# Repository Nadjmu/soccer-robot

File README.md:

# soccer-robot
This repository contains the schematic, the board design, the mechanical design (3D CAD Models) and the code for our autonomous soccer robot when we participated in the Soccer Lightweight League at the RoboCup Junior 2019. 

The rules can be found on the following website: https://junior.robocup.org/soccer/

The design of the motherboard and the ground board was done with Autodesk Eagle. The design of the mechanical components was done with the CAD Software Autodesk Inventor. The software was written with Arduino. 

This is a video where we played against Russia in the European Championship: https://www.youtube.com/watch?v=PZbQC_VygyU

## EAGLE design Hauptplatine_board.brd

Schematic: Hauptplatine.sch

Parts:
BODEN: PINHD-1X5; 1X05
C1: 0.33 uF; 1206
C2: 0.1 uF; 1206
C3: RAD 470/25; E5-10,5
C4, C6, C8, C10, C12, C14, C15, C18, C19, C22, C23, C27, C29, C31, C35, C37, C39, C43, C47, C49, C51, C53, C55, C79, C81: 1u; 1206
C5, C7, C9, C11, C13, C16, C17, C20, C21, C24, C26, C28, C30, C32, C36, C38, C40, C44, C48, C50, C52, C54, C56, C80, C82: 100n; 1206
C59: 0,33 uF; 1206
C60: 0,1uF; 1206
D1, D4: LED 6mm weiß; L3R2-08
D2, D3, D5: SFH205
D16: LED 6mm gruen; L3R2-08
F1, F2: SH22,5
IR1, IR2, IR3, IR4, IR5, IR6, IR7, IR8, IR9, IR10, IR11, IR12, IR13, IR14, IR15, IR16, IR17, IR18, IR19, IR20, IR21, IR23, IR24, IR25, IR26: TSOP4038; TSOP581X
JP1, JP2, JP3: PINHD-1X5; 1X05
JP4, JP7: PINHD-1X2; 1X02
JP5, JP6: PINHD-1X3; 1X03
LED1, LED2, LED3: LED3MM
MAGNETFELD: PINHD-1X4; 1X04
PIXY1: PINHD-2X3; 2X03
PL3: STLZ950G2; S940_2
R1, R20, R22, R24, R26, R28, R30, R32, R35, R41, R47, R50, R53, R56, R59, R62, R65, R68, R71, R74, R77, R79, R80, R85, R86, R87, R93, R95, R141, R144: 4.7k; 1206
R2, R3, R4: 60R; 1206
R5, R6, R7: 5k; 1206
R19, R21, R23, R25, R27, R29, R31, R34, R40, R46, R49, R52, R55, R58, R61, R64, R67, R70, R73, R76, R84, R92, R94, R140, R143: 100k; 1206
R33, R36, R37, R38, R39, R42, R43, R44, R45, R48, R51, R54, R57, R60, R63, R66, R69, R72, R75, R78, R124, R127, R128, R142, R145: 10R; 1206
S1, S2: KSM611A
SW1, SW2: Schukat_MS111; MSS13ASP
U$1, U$6: MOTOR_DRIVER_MODULE
U$28: BLUETOTHA
U$32: TEENSY_3.6_ALL_PINS
U$58: LOGICLEVEL
X1: ANALOG/DIGITAL-MUX-BREAKOUT

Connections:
3.3V: U$32.3.3V, U$32.3.3V3 (3.3V), U$32.3.3V4 (3.3V)
+3V3: BODEN.1, F2.2, MAGNETFELD.1, R5.1, R6.1, R7.1, R20.2, R22.2, R24.2, R26.2, R28.2, R30.2, R32.2, R33.2, R35.2, R36.2, R37.2, R38.2, R39.2, R41.2, R42.2, R43.2, R44.2, R45.2, R47.2, R48.2, R50.2, R51.2, R53.2, R54.2, R56.2, R57.2, R59.2, R60.2, R62.2, R63.2, R65.2, R66.2, R68.2, R69.2, R71.2, R72.2, R74.2, R75.2, R77.2, R78.2, R79.2, R80.2, R87.2, R93.2, R95.2, R124.2, R127.2, R128.2, R141.2, R142.2, R144.2, R145.2, U$28.VCC, U$58.9 (LV), X1.VCC
+5V: BODEN.3, C2.2, JP1.1, JP2.1, JP3.1, JP6.3, PIXY1.2, R2.1, R3.1, R4.1, U$1.+5V, U$6.+5V, U$32.VIN, U$32.VUSB, U$58.3 (HV)
+12V: C1.2, C3.+, C59.2, F1.1, JP5.1, JP6.1, R86.2, SW2.U (U1)
+12V1: R1.2, SW2.2 (R1), U$1.VCC@1 (VCC), U$1.VCC@2 (VCC), U$1.VCC@3 (VCC), U$6.VCC@1 (VCC), U$6.VCC@2 (VCC), U$6.VCC@3 (VCC)
AA_00: U$32.32/A13 (32/A13/TX4/SCK1), X1.SIG (COM)
AREF: U$32.AREF
A_01: C4.1, R19.2, X1.P$16 (16)
A_02: C6.1, R21.2, X1.P$15 (15)
A_03: C8.1, R23.2, X1.P$14 (14)
A_04: C10.1, R25.2, X1.P$13 (13)
A_05: C14.1, R49.2, X1.P$12 (12)
A_06: C12.1, R27.2, X1.P$11 (11)
A_07: C18.1, R55.2, X1.P$10 (10)
A_08: C15.1, R29.2, X1.P$9 (9)
A_09: C19.1, R31.2, X1.P$7 (7)
A_10: C23.1, R34.2, X1.P$8 (8)
A_11: C27.1, R40.2, U$32.23/A9 (23/A9/T/PWM)
A_12: C31.1, R46.2, U$32.39/A20
A_13: C35.1, R52.2, U$32.A21 (A21/DAC0)
A_14: C39.1, R58.2, U$32.21/A7 (21/A7/PWM)
A_15: C22.1, R61.2, U$32.22/A8 (22/A8/T/PWM)
A_16: C43.1, R64.2, U$32.34/A15 (34/A15/RX5/CAN1-RX)
A_17: C29.1, R67.2, U$32.35/A16 (35/A16/PWM)
A_18: C47.1, R70.2, U$32.36/A17 (36/A17/PWM)
A_19: C49.1, R73.2, U$32.37/A18 (37/A18/SCL1/PWM)
A_20: C51.1, R76.2, U$32.38/A19 (38/A19/SDA1/PWM)
A_21: C37.1, R84.2, U$32.33/A14 (33/A14/TX5/CAN1-TX)
A_24: C53.1, R92.2, X1.P$4 (4)
A_25: C79.1, R140.2, U$32.A11
A_26: C55.1, R94.2, X1.P$5 (5)
A_27: C81.1, R143.2, X1.P$6 (6)
D1.1__FW: U$1.M1_FW_SIG (IN1_FW), U$32.14/A0 (14/A0/PWM)
D1.2__RW: U$1.M1_RW_SIG (IN1_RW), U$32.20/A6 (20/A6/PWM)
D2.1__FW: U$1.M2_FW_SIG (IN2_FW), U$32.A22 (A22/DAC1)
D2.2__RW: U$1.M2_RW_SIG (IN2_RW), U$32.15/A1 (15/A1/T)
D3.1__FW: U$6.M1_FW_SIG (IN1_FW), U$32.16/A2 (16/A2/T/PWM)
D3.2__RW: U$6.M1_RW_SIG (IN1_RW), U$32.17/A3 (17/A3/T/PWM)
GND: BODEN.2, C1.1, C2.1, C3.-, C4.2, C5.2, C6.2, C7.2, C8.2, C9.2, C10.2, C11.2, C12.2, C13.2, C14.2, C15.2, C16.2, C17.2, C18.2, C19.2, C20.2, C21.2, C22.2, C23.2, C24.2, C26.2, C27.2, C28.2, C29.2, C30.2, C31.2, C32.2, C35.2, C36.2, C37.2, C38.2, C39.2, C40.2, C43.2, C44.2, C47.2, C48.2, C49.2, C50.2, C51.2, C52.2, C53.2, C54.2, C55.2, C56.2, C59.1, C60.1, C79.2, C80.2, C81.2, C82.2, D1.2 (K), D2.A, D3.A, D4.2 (K), D5.A, D16.2 (K), IR1.2 (GND), IR2.2 (GND), IR3.2 (GND), IR4.2 (GND), IR5.2 (GND), IR6.2 (GND), IR7.2 (GND), IR8.2 (GND), IR9.2 (GND), IR10.2 (GND), IR11.2 (GND), IR12.2 (GND), IR13.2 (GND), IR14.2 (GND), IR15.2 (GND), IR16.2 (GND), IR17.2 (GND), IR18.2 (GND), IR19.2 (GND), IR20.2 (GND), IR21.2 (GND), IR23.2 (GND), IR24.2 (GND), IR25.2 (GND), IR26.2 (GND), JP1.5, JP2.5, JP3.5, JP5.2, JP6.2, LED1.K (C), LED2.K (C), LED3.K (C), MAGNETFELD.4, PIXY1.6, PL3.2, S1.A, S1.C, S2.A, S2.C, U$1.GND@1 (GND), U$1.GND@2 (GND), U$1.GND@3 (GND), U$1.GND@4 (GND), U$6.GND@1 (GND), U$6.GND@2 (GND), U$6.GND@3 (GND), U$6.GND@4 (GND), U$28.GND, U$32.AGND, U$32.GND, U$32.GND1 (GND), U$32.GND3 (GND), U$32.GND4 (GND), U$32.GND6 (GND), U$58.4 (GND), U$58.10 (GND1), X1.GND
K1: R79.1, S1.B, S1.D, U$32.24
K2: R80.1, S2.B, S2.D, U$32.4 (4/CAN0-RX/SDA2/PWM)
LI1: D5.K (C), R6.2, X1.P$1 (1)
LI2: D3.K (C), R5.2, X1.P$2 (2)
LI3: D2.K (C), R7.2, X1.P$3 (3)
MISO: PIXY1.1, U$32.12 (12/MISO0)
MOSI: PIXY1.4, U$32.11 (11/MOSI0)
unnamed: JP4.2, U$6.M1_FW (OUT1_FW)
unnamed: F1.2, SW1.1 (A1)
unnamed: JP4.1, U$6.M1_RW (OUT1_RW)
unnamed: C60.2, F2.1, JP5.3
unnamed: JP7.2, U$6.M2_FW (OUT2_FW)
unnamed: JP7.1, U$6.M2_RW (OUT2_RW)
unnamed: LED3.A, R2.2
unnamed: LED1.A, R3.2
unnamed: LED2.A, R4.2
unnamed: D4.1 (A), R1.1
unnamed: PL3.1, R85.2, SW1.U (U1)
unnamed: IR1.1 (VO), R19.1, R20.1
unnamed: C5.1, IR1.3 (VS), R33.1
unnamed: IR2.1 (VO), R21.1, R22.1
unnamed: C7.1, IR2.3 (VS), R36.1
unnamed: IR3.1 (VO), R23.1, R24.1
unnamed: C9.1, IR3.3 (VS), R37.1
unnamed: IR4.1 (VO), R25.1, R26.1
unnamed: C11.1, IR4.3 (VS), R38.1
unnamed: IR6.1 (VO), R27.1, R28.1
unnamed: C13.1, IR6.3 (VS), R39.1
unnamed: IR8.1 (VO), R29.1, R30.1
unnamed: IR9.1 (VO), R31.1, R32.1
unnamed: C20.1, IR9.3 (VS), R43.1
unnamed: IR10.1 (VO), R34.1, R35.1
unnamed: C24.1, IR10.3 (VS), R44.1
unnamed: C16.1, IR8.3 (VS), R42.1
unnamed: IR5.1 (VO), R49.1, R50.1
unnamed: IR11.1 (VO), R40.1, R41.1
unnamed: C28.1, IR11.3 (VS), R45.1
unnamed: IR12.1 (VO), R46.1, R47.1
unnamed: C32.1, IR12.3 (VS), R48.1
unnamed: C17.1, IR5.3 (VS), R51.1
unnamed: IR7.1 (VO), R55.1, R56.1
unnamed: C21.1, IR7.3 (VS), R57.1
unnamed: IR15.1 (VO), R61.1, R62.1
unnamed: C26.1, IR15.3 (VS), R63.1
unnamed: IR17.1 (VO), R67.1, R68.1
unnamed: C30.1, IR17.3 (VS), R69.1
unnamed: IR21.1 (VO), R84.1, R87.1
unnamed: C38.1, IR21.3 (VS), R124.1
unnamed: IR13.1 (VO), R52.1, R53.1
unnamed: C36.1, IR13.3 (VS), R54.1
unnamed: IR14.1 (VO), R58.1, R59.1
unnamed: C40.1, IR14.3 (VS), R60.1
unnamed: IR23.1 (VO), R92.1, R93.1
unnamed: C54.1, IR23.3 (VS), R127.1
unnamed: IR25.1 (VO), R94.1, R95.1
unnamed: C56.1, IR25.3 (VS), R128.1
unnamed: IR16.1 (VO), R64.1, R65.1
unnamed: C44.1, IR16.3 (VS), R66.1
unnamed: IR18.1 (VO), R70.1, R71.1
unnamed: C48.1, IR18.3 (VS), R72.1
unnamed: IR19.1 (VO), R73.1, R74.1
unnamed: C50.1, IR19.3 (VS), R75.1
unnamed: IR20.1 (VO), R76.1, R77.1
unnamed: C52.1, IR20.3 (VS), R78.1
unnamed: IR24.1 (VO), R140.1, R141.1
unnamed: C80.1, IR24.3 (VS), R142.1
unnamed: IR26.1 (VO), R143.1, R144.1
unnamed: C82.1, IR26.3 (VS), R145.1
unnamed: D16.1 (A), R85.1
unnamed: D1.1 (A), R86.1
PWM_M1: U$1.M1_PWM_SIG (IN1_PWM), U$32.5 (5/PWM)
PWM_M2: U$1.M2_PWM_SIG (IN2_PWM), U$32.6 (6/PWM)
PWM_M3: U$6.M1_PWM_SIG (IN1_PWM), U$32.29 (29/T/PWM)
RX2: BODEN.5, U$32.9 (9/RX2/PWM)
RXB: U$28.TX, U$32.7 (7/RX3/PWM)
SCK: PIXY1.3, U$32.13 (13/SCK0/LED)
SCL_2: MAGNETFELD.2, U$32.19/A5 (19/A5/T/SCL0), U$58.8 (LV2)
SCL_ULT: JP1.3, JP2.3, JP3.3, U$58.2 (HV2)
SDA_2: MAGNETFELD.3, U$32.18/A4 (18/A4/T/SDA0), U$58.7 (LV1)
SDA_ULT: JP1.2, JP2.2, JP3.2, U$58.1 (HV1)
S_0: U$32.0 (0/RX1/MOSI1/T), X1.S0
S_1: U$32.1 (1/TX1/MISO1/T), X1.S1
S_2: U$32.2 (2/PWM), X1.S2
S_3: U$32.3 (3/CAN0-TX/SCL2/PWM), X1.S3
TX2: BODEN.4, U$32.10 (10/TX2/PWM)
TXB: U$28.RX, U$32.8 (8/TX3/PWM)
VBAT: U$32.VBAT
VUSB1: U$32.VUSB1

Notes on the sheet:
Akku
VCC
GND
LED akku angeschlossen
LED Roboter an
+5V
Torwrt
feldspieler
magnetfeld
sicherung 16 A (Träge)
sicherung 1 A
echter NAME TSSP4038
0.1uF und 100nF ist Dasselbe!!!!!!!!!!!!!!!!!!!!!!!!!!!!!!!!!!!!!!!!!!!!!!!!!!!!!!!!!!!!!!!!!!!!!!!!
3,3 V wandler
LED Motoren an

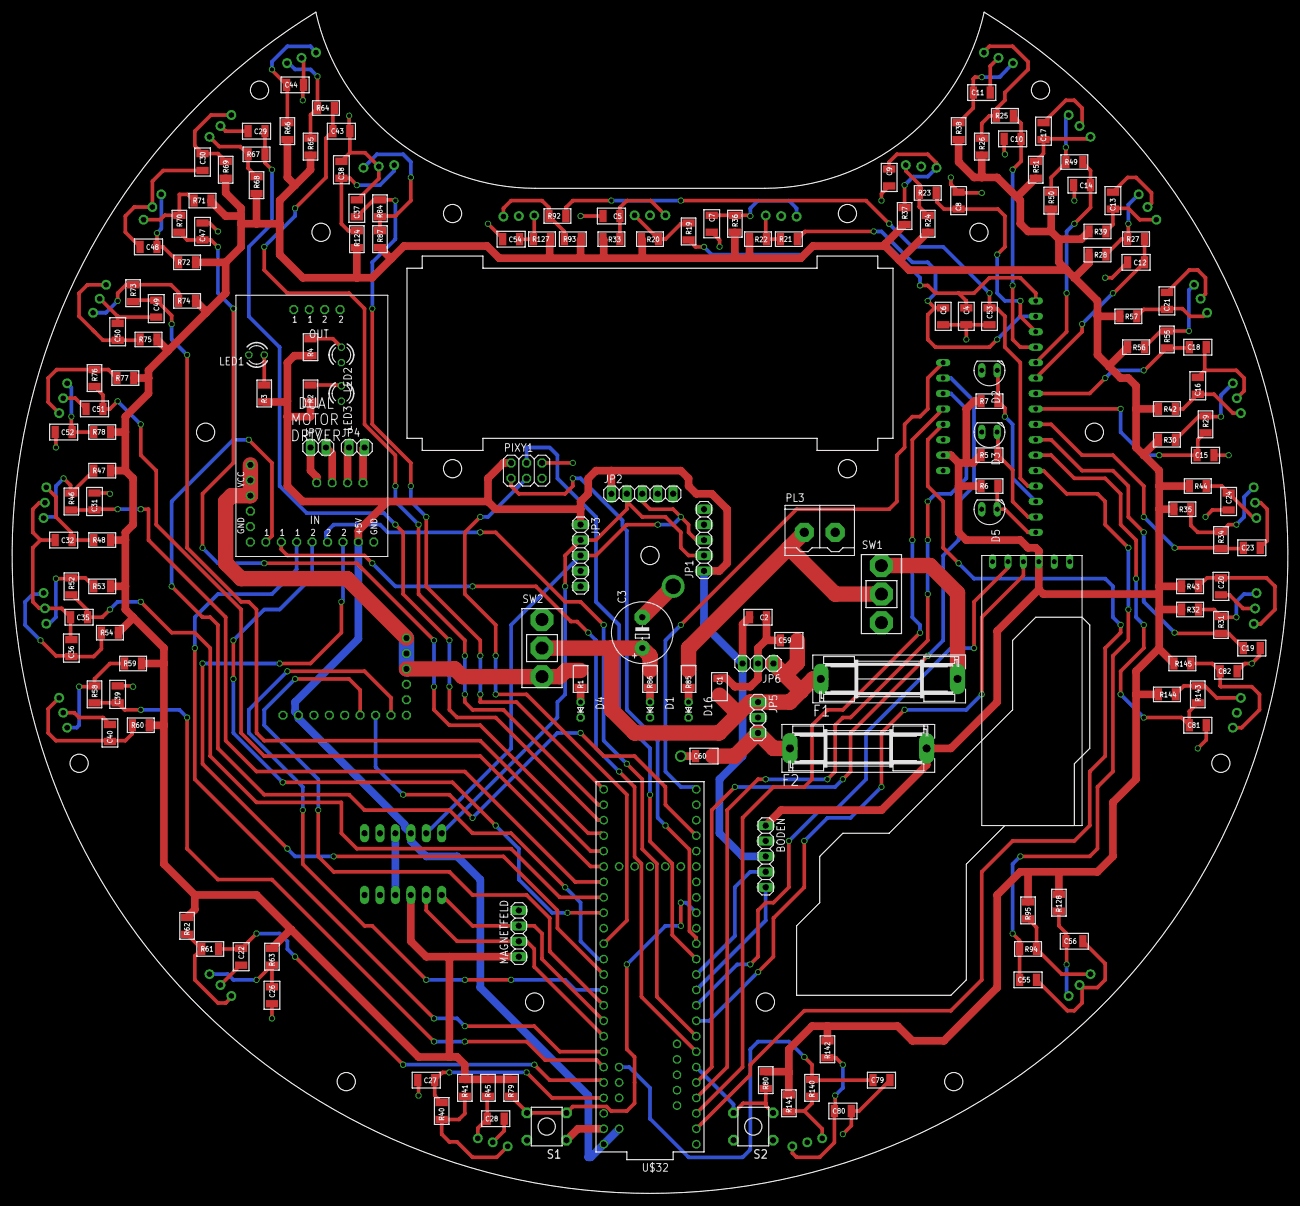
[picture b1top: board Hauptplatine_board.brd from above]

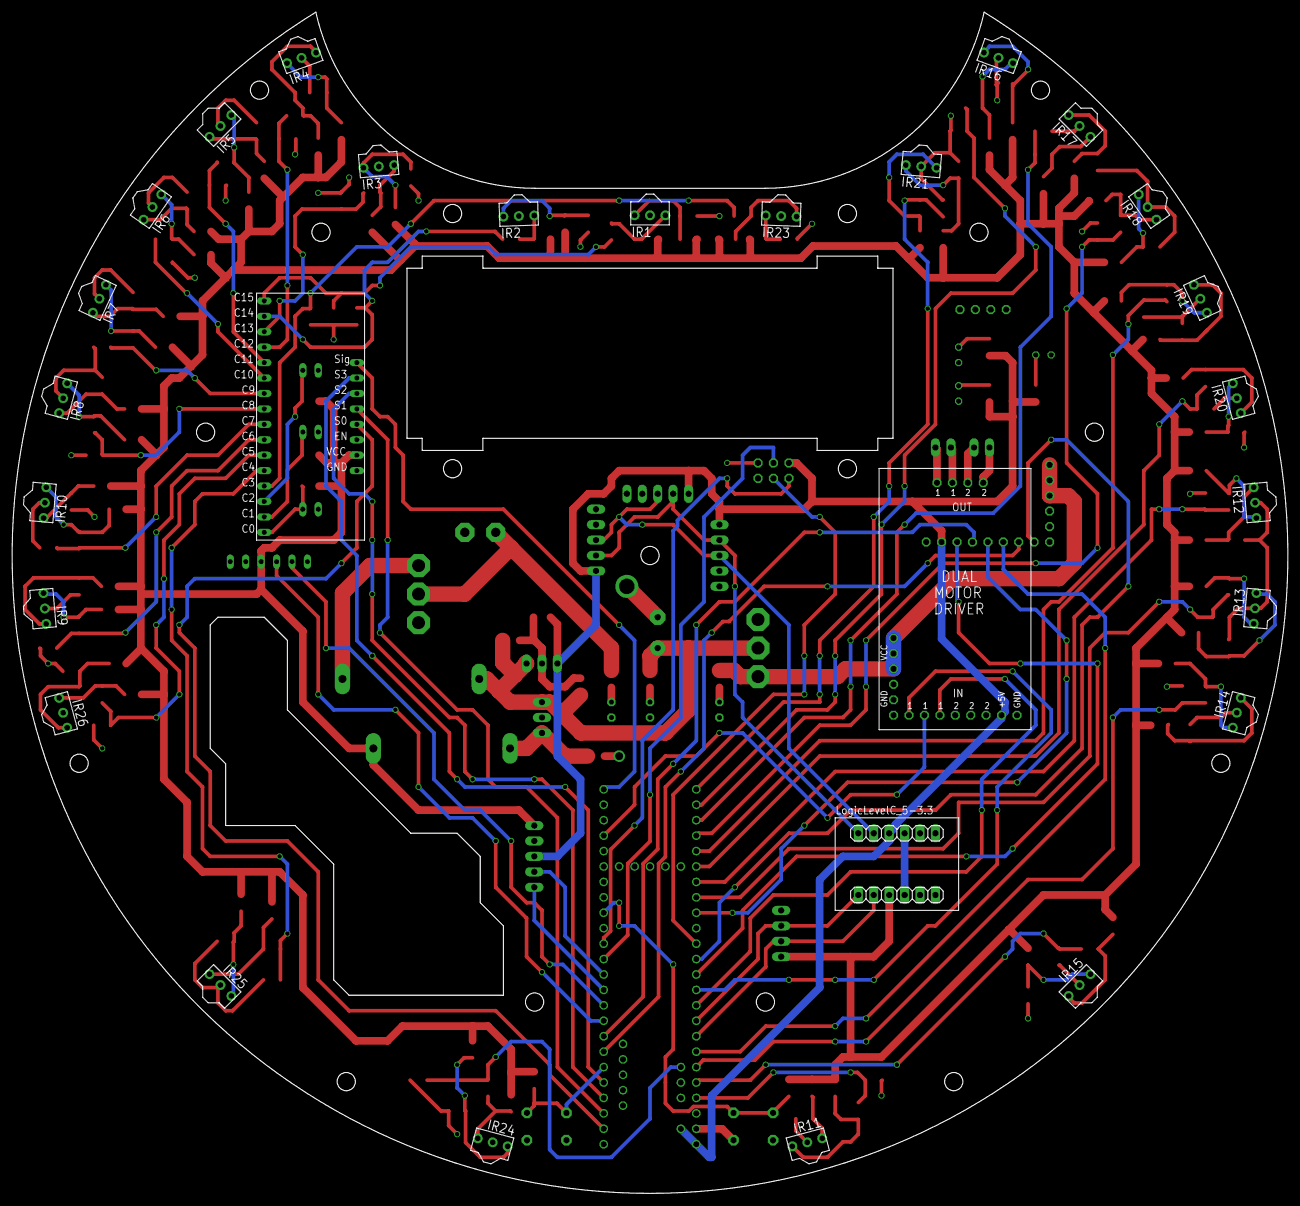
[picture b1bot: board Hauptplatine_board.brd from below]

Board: 2 copper layers, 210.0 x 194.4 mm, 198 parts (28 on the bottom side), 124 nets.

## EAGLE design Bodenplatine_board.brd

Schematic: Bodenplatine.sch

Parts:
D1, D2, D3, D4, D5, D6, D7, D8, D9, D10, D11, D13, D14, D15, D16, D17, D18, D19, D20, D21, D22, D23, D24, D25, D26, D27, D28, D29, D30, D34, D35, D36, D37: SFH205
JP1: PINHD-1X5; 1X05
LED1, LED2, LED3, LED4, LED5, LED6, LED7, LED8, LED9, LED10, LED11, LED12, LED14, LED15, LED16, LED17, LED18, LED19, LED20, LED21, LED22, LED23, LED24, LED25, LED26, LED27, LED28, LED29, LED30, LED31, LED32, LED33, LED34, LED38, LED40, LED41, LED42: LED3MM
R1, R2, R4, R5, R8, R10, R14, R15, R17, R19, R21, R23, R26, R28, R29, R30, R32, R34, R38, R40, R41, R42, R43, R45, R47, R48, R49, R50, R52, R54, R55, R56, R58, R59, R61, R62, R68: 60R; 1206
R3, R6, R7, R9, R11, R12, R13, R16, R18, R20, R22, R24, R25, R27, R31, R33, R35, R36, R39, R44, R46, R51, R53, R64, R65, R66, R67, R71, R72, R73, R78, R79, R80: 5k; 1206
U$32: TEENSY_3.6_ALL_PINS
X1: ANALOG/DIGITAL-MUX-BREAKOUT

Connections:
3.3V: U$32.3.3V, U$32.3.3V3 (3.3V), U$32.3.3V4 (3.3V)
+3V3: JP1.1, R3.1, R6.1, R7.1, R9.1, R11.1, R12.1, R13.1, R16.1, R18.1, R20.1, R22.1, R24.1, R25.1, R27.1, R31.1, R33.1, R35.1, R36.1, R39.1, R44.1, R46.1, R51.1, R53.1, R64.1, R65.1, R66.1, R67.1, R71.1, R72.1, R73.1, R78.1, R79.1, R80.1, X1.VCC
+5V: JP1.3, R1.1, R2.1, R4.1, R5.1, R8.1, R10.1, R14.1, R15.1, R17.1, R19.1, R21.1, R23.1, R26.1, R28.1, R29.1, R30.1, R32.2, R34.1, R38.1, R40.2, R41.1, R42.2, R43.2, R45.1, R47.1, R48.1, R49.1, R50.1, R52.1, R54.1, R55.1, R56.1, R58.1, U$32.VIN, U$32.VUSB
A1: D16.K (C), R7.2, U$32.15/A1 (15/A1/T)
A2: D15.K (C), R9.2, U$32.16/A2 (16/A2/T/PWM)
A3: D14.K (C), R11.2, U$32.17/A3 (17/A3/T/PWM)
A4: D13.K (C), R13.2, U$32.18/A4 (18/A4/T/SDA0)
A5: D9.K (C), R18.2, U$32.19/A5 (19/A5/T/SCL0)
A6: D8.K (C), R20.2, U$32.20/A6 (20/A6/PWM)
A7: D7.K (C), R22.2, U$32.21/A7 (21/A7/PWM)
A8: D6.K (C), R25.2, U$32.22/A8 (22/A8/T/PWM)
A9: D5.K (C), R27.2, U$32.23/A9 (23/A9/T/PWM)
A10: D2.K (C), R33.2, U$32.A21 (A21/DAC0)
A11: D1.K (C), R35.2, U$32.A22 (A22/DAC1)
A13: D37.K (C), R64.2, U$32.32/A13 (32/A13/TX4/SCK1)
A14: D36.K (C), R65.2, U$32.33/A14 (33/A14/TX5/CAN1-TX)
A15: D35.K (C), R66.2, U$32.34/A15 (34/A15/RX5/CAN1-RX)
A16: D34.K (C), R67.2, U$32.35/A16 (35/A16/PWM)
A17: D30.K (C), R71.2, U$32.36/A17 (36/A17/PWM)
A18: D29.K (C), R72.2, U$32.37/A18 (37/A18/SCL1/PWM)
A19: D28.K (C), R73.2, X1.P$1 (1)
A20: D23.K (C), R78.2, X1.P$2 (2)
A21: D22.K (C), R79.2, X1.P$3 (3)
A22: D21.K (C), R80.2, X1.P$4 (4)
A23: D3.K (C), R3.2, X1.P$5 (5)
A24: D4.K (C), R6.2, X1.P$6 (6)
A25: D10.K (C), R12.2, X1.P$7 (7)
A26: D11.K (C), R16.2, X1.P$8 (8)
A27: D17.K (C), R24.2, X1.P$9 (9)
A28: D18.K (C), R31.2, X1.P$10 (10)
A29: D19.K (C), R36.2, X1.P$11 (11)
A30: D20.K (C), R39.2, X1.P$12 (12)
A31: D24.K (C), R44.2, X1.P$13 (13)
A32: D25.K (C), R46.2, X1.P$14 (14)
A33: D26.K (C), R51.2, X1.P$15 (15)
A34: D27.K (C), R53.2, X1.P$16 (16)
AREF: U$32.AREF
GND: D1.A, D2.A, D3.A, D4.A, D5.A, D6.A, D7.A, D8.A, D9.A, D10.A, D11.A, D13.A, D14.A, D15.A, D16.A, D17.A, D18.A, D19.A, D20.A, D21.A, D22.A, D23.A, D24.A, D25.A, D26.A, D27.A, D28.A, D29.A, D30.A, D34.A, D35.A, D36.A, D37.A, JP1.2, LED1.K (C), LED2.K (C), LED3.K (C), LED4.K (C), LED5.K (C), LED6.K (C), LED7.K (C), LED8.K (C), LED9.K (C), LED10.K (C), LED11.K (C), LED12.K (C), LED14.K (C), LED15.K (C), LED16.K (C), LED17.K (C), LED18.K (C), LED19.K (C), LED20.K (C), LED21.K (C), LED22.K (C), LED23.K (C), LED24.K (C), LED25.K (C), LED26.K (C), LED27.K (C), LED28.K (C), LED29.K (C), LED30.K (C), LED31.K (C), LED32.K (C), LED33.K (C), LED34.K (C), LED38.K (C), LED40.K (C), LED41.K (C), LED42.K (C), U$32.AGND, U$32.GND, U$32.GND1 (GND), U$32.GND3 (GND), U$32.GND4 (GND), U$32.GND6 (GND), X1.GND
unnamed: LED8.A, R1.2
unnamed: LED11.A, R2.2
unnamed: LED23.A, R5.2
unnamed: LED10.A, R4.2
unnamed: LED24.A, R8.2
unnamed: LED25.A, R15.2
unnamed: LED26.A, R21.2
unnamed: LED27.A, R29.2
unnamed: LED28.A, R34.2
unnamed: LED9.A, R10.2
unnamed: LED29.A, R38.2
unnamed: LED30.A, R40.1
unnamed: LED12.A, R23.2
unnamed: LED31.A, R45.2
unnamed: LED32.A, R47.2
unnamed: LED7.A, R14.2
unnamed: LED33.A, R52.2
unnamed: LED6.A, R17.2
unnamed: LED3.A, R32.1
unnamed: LED5.A, R19.2
unnamed: LED34.A, R58.2
unnamed: LED41.A, R59.2
unnamed: LED42.A, R61.2
unnamed: LED40.A, R62.2
unnamed: LED38.A, R68.2
unnamed: LED4.A, R26.2
unnamed: LED2.A, R28.2
unnamed: LED1.A, R30.2
unnamed: R68.1, U$32.5 (5/PWM)
unnamed: LED22.A, R41.2
unnamed: LED21.A, R42.1
unnamed: LED20.A, R43.1
unnamed: LED19.A, R48.2
unnamed: LED18.A, R49.2
unnamed: LED17.A, R50.2
unnamed: LED16.A, R54.2
unnamed: LED15.A, R55.2
unnamed: LED14.A, R56.2
RIX2: R62.1, U$32.4 (4/CAN0-RX/SDA2/PWM)
RIX3: R61.1, U$32.3 (3/CAN0-TX/SCL2/PWM)
RIX4: R59.1, U$32.2 (2/PWM)
RX: JP1.5, U$32.1 (1/TX1/MISO1/T)
SIG: U$32.31/A12 (31/A12/RX4), X1.SIG (COM)
S_0: U$32.24, X1.S0
S_1: U$32.12 (12/MISO0), X1.S1
S_2: U$32.11 (11/MOSI0), X1.S2
S_3: U$32.10 (10/TX2/PWM), X1.S3
TX: JP1.4, U$32.0 (0/RX1/MOSI1/T)
VBAT: U$32.VBAT
VUSB1: U$32.VUSB1

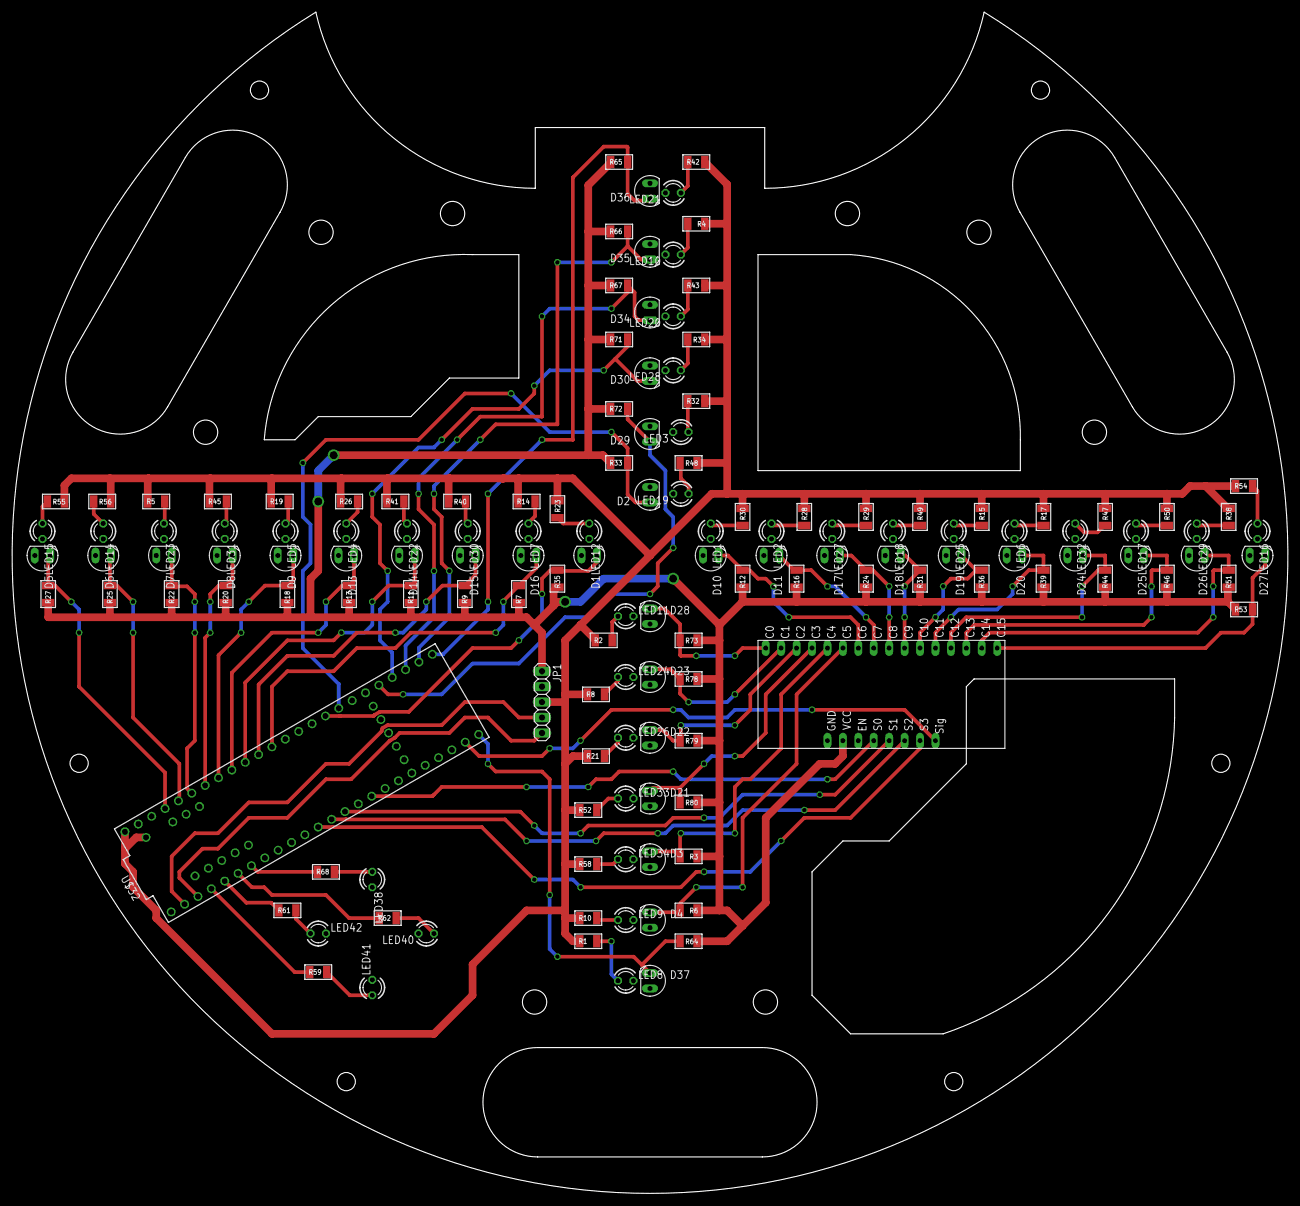
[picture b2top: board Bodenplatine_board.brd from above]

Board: 2 copper layers, 210.0 x 194.4 mm, 143 parts (0 on the bottom side), 85 nets.

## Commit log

2025-11-03 Fix grammatical error in README description
2025-11-03 Update README with RoboCup rules link
    Added a link to the RoboCup Junior soccer rules.
2025-11-03 Enhance README with design tools and video link
    Added additional details about design tools and a video link.
2025-11-03 Add LICENSE file
